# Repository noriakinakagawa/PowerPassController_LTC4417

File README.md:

# PowerPassController_LTC4417
LTC4417を使ったパワーパスコントローラ。安定化電源側のコネクタを抜くと瞬時にバッテリ側から電力が供給される。
バッテリ電圧が安定化電源より高くても安定化電源側を優先するので、理想ダイオードで冗長にしたものよりスマートに使える。
また、過電圧保護と低電圧保護も設定できるので、供給カットによりリチウム系バッテリの過放電を保護する。
部品は秋葉原で手に入る範囲に絞った。

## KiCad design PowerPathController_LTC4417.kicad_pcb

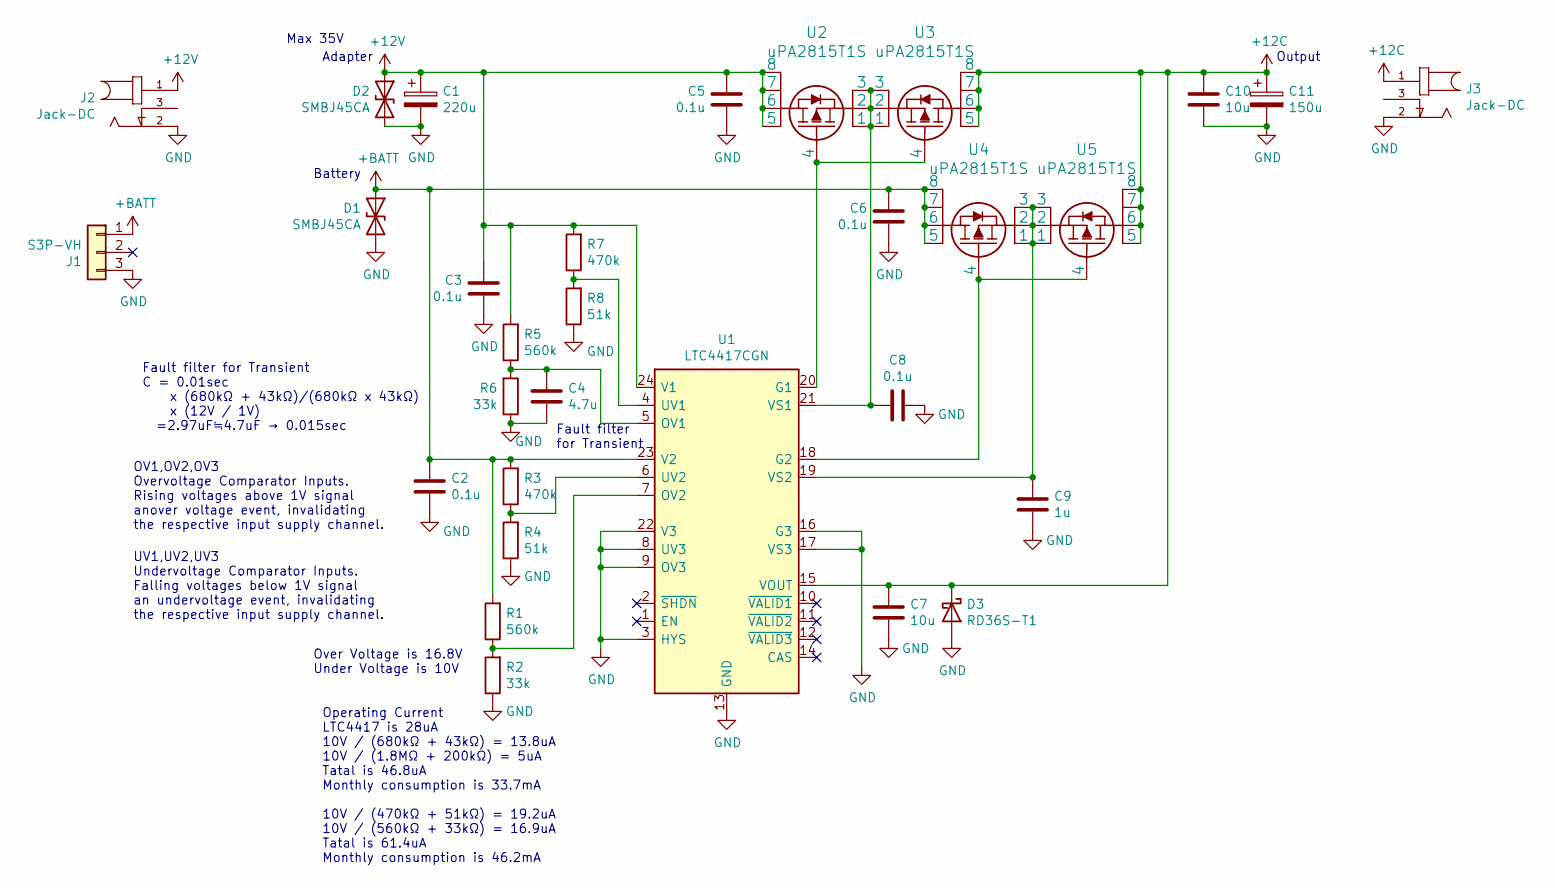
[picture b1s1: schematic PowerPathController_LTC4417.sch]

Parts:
C1: 220u; CP_Radial_D8.0mm_P3.50mm
C2, C3, C5, C6, C8: 0.1u; C_0603
C4: 4.7u; C_0805
C7, C10: 10u; C_1210
C9: 1u; C_0603
C11: 150u; CP_Radial_D10.0mm_P5.00mm
D1, D2: SMBJ45CA; D_SMB
D3: RD36S-T1; D_0603
J1: S3P-VH; JST_VH_S3P-VH_1x03_P3.96mm_Horizontal
J2, J3: Jack-DC; CUI_PJ-002B
R1, R5: 560k; R_Axial_DIN0207_L6.3mm_D2.5mm_P2.54mm_Vertical
R2, R6: 33k; R_Axial_DIN0207_L6.3mm_D2.5mm_P2.54mm_Vertical
R3, R7: 470k; R_Axial_DIN0207_L6.3mm_D2.5mm_P2.54mm_Vertical
R4, R8: 51k; R_Axial_DIN0207_L6.3mm_D2.5mm_P2.54mm_Vertical
U1: LTC4417CGN; SSOP-24_3.9x8.7mm_Pitch0.635mm
U2, U3, U4, U5: uPA2815T1S; UPA2815T1S-E2-AT

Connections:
+12C: C7.1, C10.1, C11.1, D3.1 (K), J3.1, U1.15 (VOUT), U3.5, U3.6, U3.7, U3.8, U5.5, U5.6, U5.7, U5.8
+12V: C1.1, C3.1, C5.1, D2.1 (A1), J2.1, R5.2, R7.2, U1.24 (V1), U2.5, U2.6, U2.7, U2.8
+BATT: C2.1, C6.1, D1.1 (A1), J1.1, R1.2, R3.2, U1.23 (V2), U4.5, U4.6, U4.7, U4.8
GND: C1.2, C2.2, C3.2, C4.2, C5.2, C6.2, C7.2, C8.2, C9.2, C10.2, C11.2, D1.2 (A2), D2.2 (A2), D3.2 (A), J1.3, J2.2, J3.2, R2.1, R4.1, R6.1, R8.1, U1.3 (HYS), U1.8 (UV3), U1.9 (OV3), U1.13 (GND), U1.16 (G3), U1.17 (VS3), U1.22 (V3)
unnamed: C4.1, R5.1, R6.2, U1.5 (OV1)
unnamed: C8.1, U1.21 (VS1), U2.1, U2.2, U2.3, U3.1, U3.2, U3.3
unnamed: C9.1, U1.19 (VS2), U4.1, U4.2, U4.3, U5.1, U5.2, U5.3
unnamed: R1.1, R2.2, U1.7 (OV2)
unnamed: R3.1, R4.2, U1.6 (UV2)
unnamed: R7.1, R8.2, U1.4 (UV1)
unnamed: U1.18 (G2), U4.4, U5.4
unnamed: U1.20 (G1), U2.4, U3.4

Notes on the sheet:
OV1,OV2,OV3 Overvoltage Comparator Inputs. Rising voltages above 1V signal anover voltage event, invalidating the respective input supply channel.
UV1,UV2,UV3 Undervoltage Comparator Inputs. Falling voltages below 1V signal an undervoltage event, invalidating the respective input supply channel.
Adapter
Battery
Output
Over Voltage is 16.8V Under Voltage is 10V
Fault filter for Transient
Fault filter for Transient C = 0.01sec x (680kΩ + 43kΩ)/(680kΩ x 43kΩ) x (12V / 1V) =2.97uF≒4.7uF → 0.015sec
Operating Current LTC4417 is 28uA 10V / (680kΩ + 43kΩ) = 13.8uA 10V / (1.8MΩ + 200kΩ) = 5uA Tatal is 46.8uA Monthly consumption is 33.7mA 10V / (470kΩ + 51kΩ) = 19.2uA 10V / (560kΩ + 33kΩ) = 16.9uA Tatal is 61.4uA Monthly consumption is 46.2mA
Max 35V

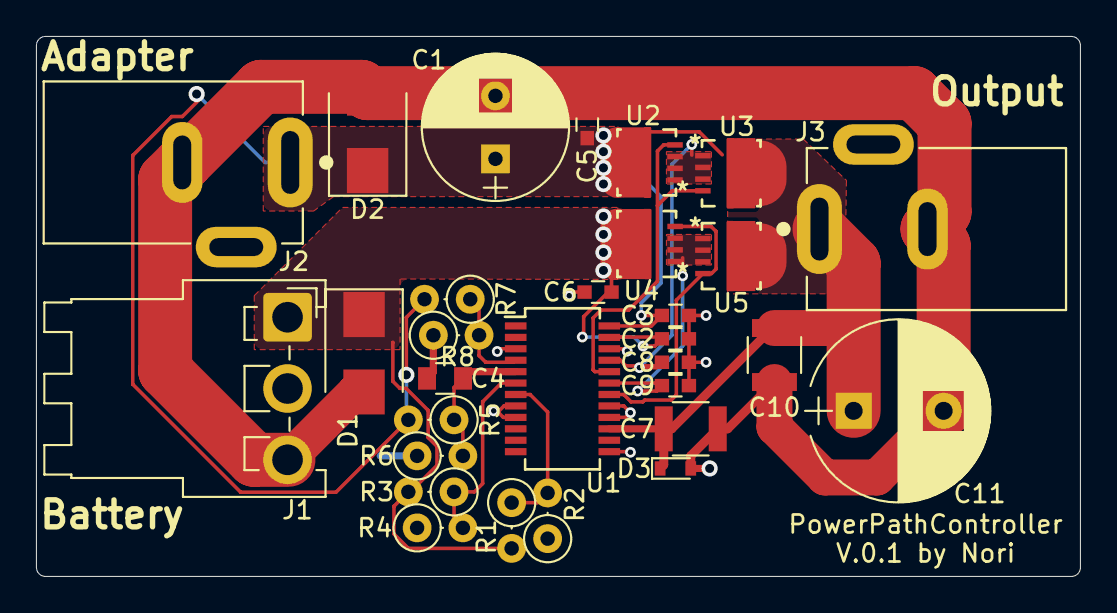
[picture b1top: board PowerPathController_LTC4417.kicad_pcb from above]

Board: 2 copper layers, 58.0 x 30.0 mm, 30 parts (0 on the bottom side), 12 nets.
